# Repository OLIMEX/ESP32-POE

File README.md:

# ESP32-POE

ESP32-PoE is an IoT WIFI/BLE/Ethernet development board with Power-Over-Ethernet feature.

The Si3402-B chip is IEEE 802.3-compliant, including pre-standard (legacy) PoE support. 

Perfect solution for Internet-of-Things that can be expanded with sensors and actuators taking power from Ethernet cable.

Low-power design consuming less then 100uA in deep sleep mode!

Product page: https://www.olimex.com/Products/IoT/ESP32/ESP32-POE/open-source-hardware

## License
* Hardware is released under Apache 2.0 License
* Software is released under GPL3 License
* Documentation is released under CC BY-SA 3.0

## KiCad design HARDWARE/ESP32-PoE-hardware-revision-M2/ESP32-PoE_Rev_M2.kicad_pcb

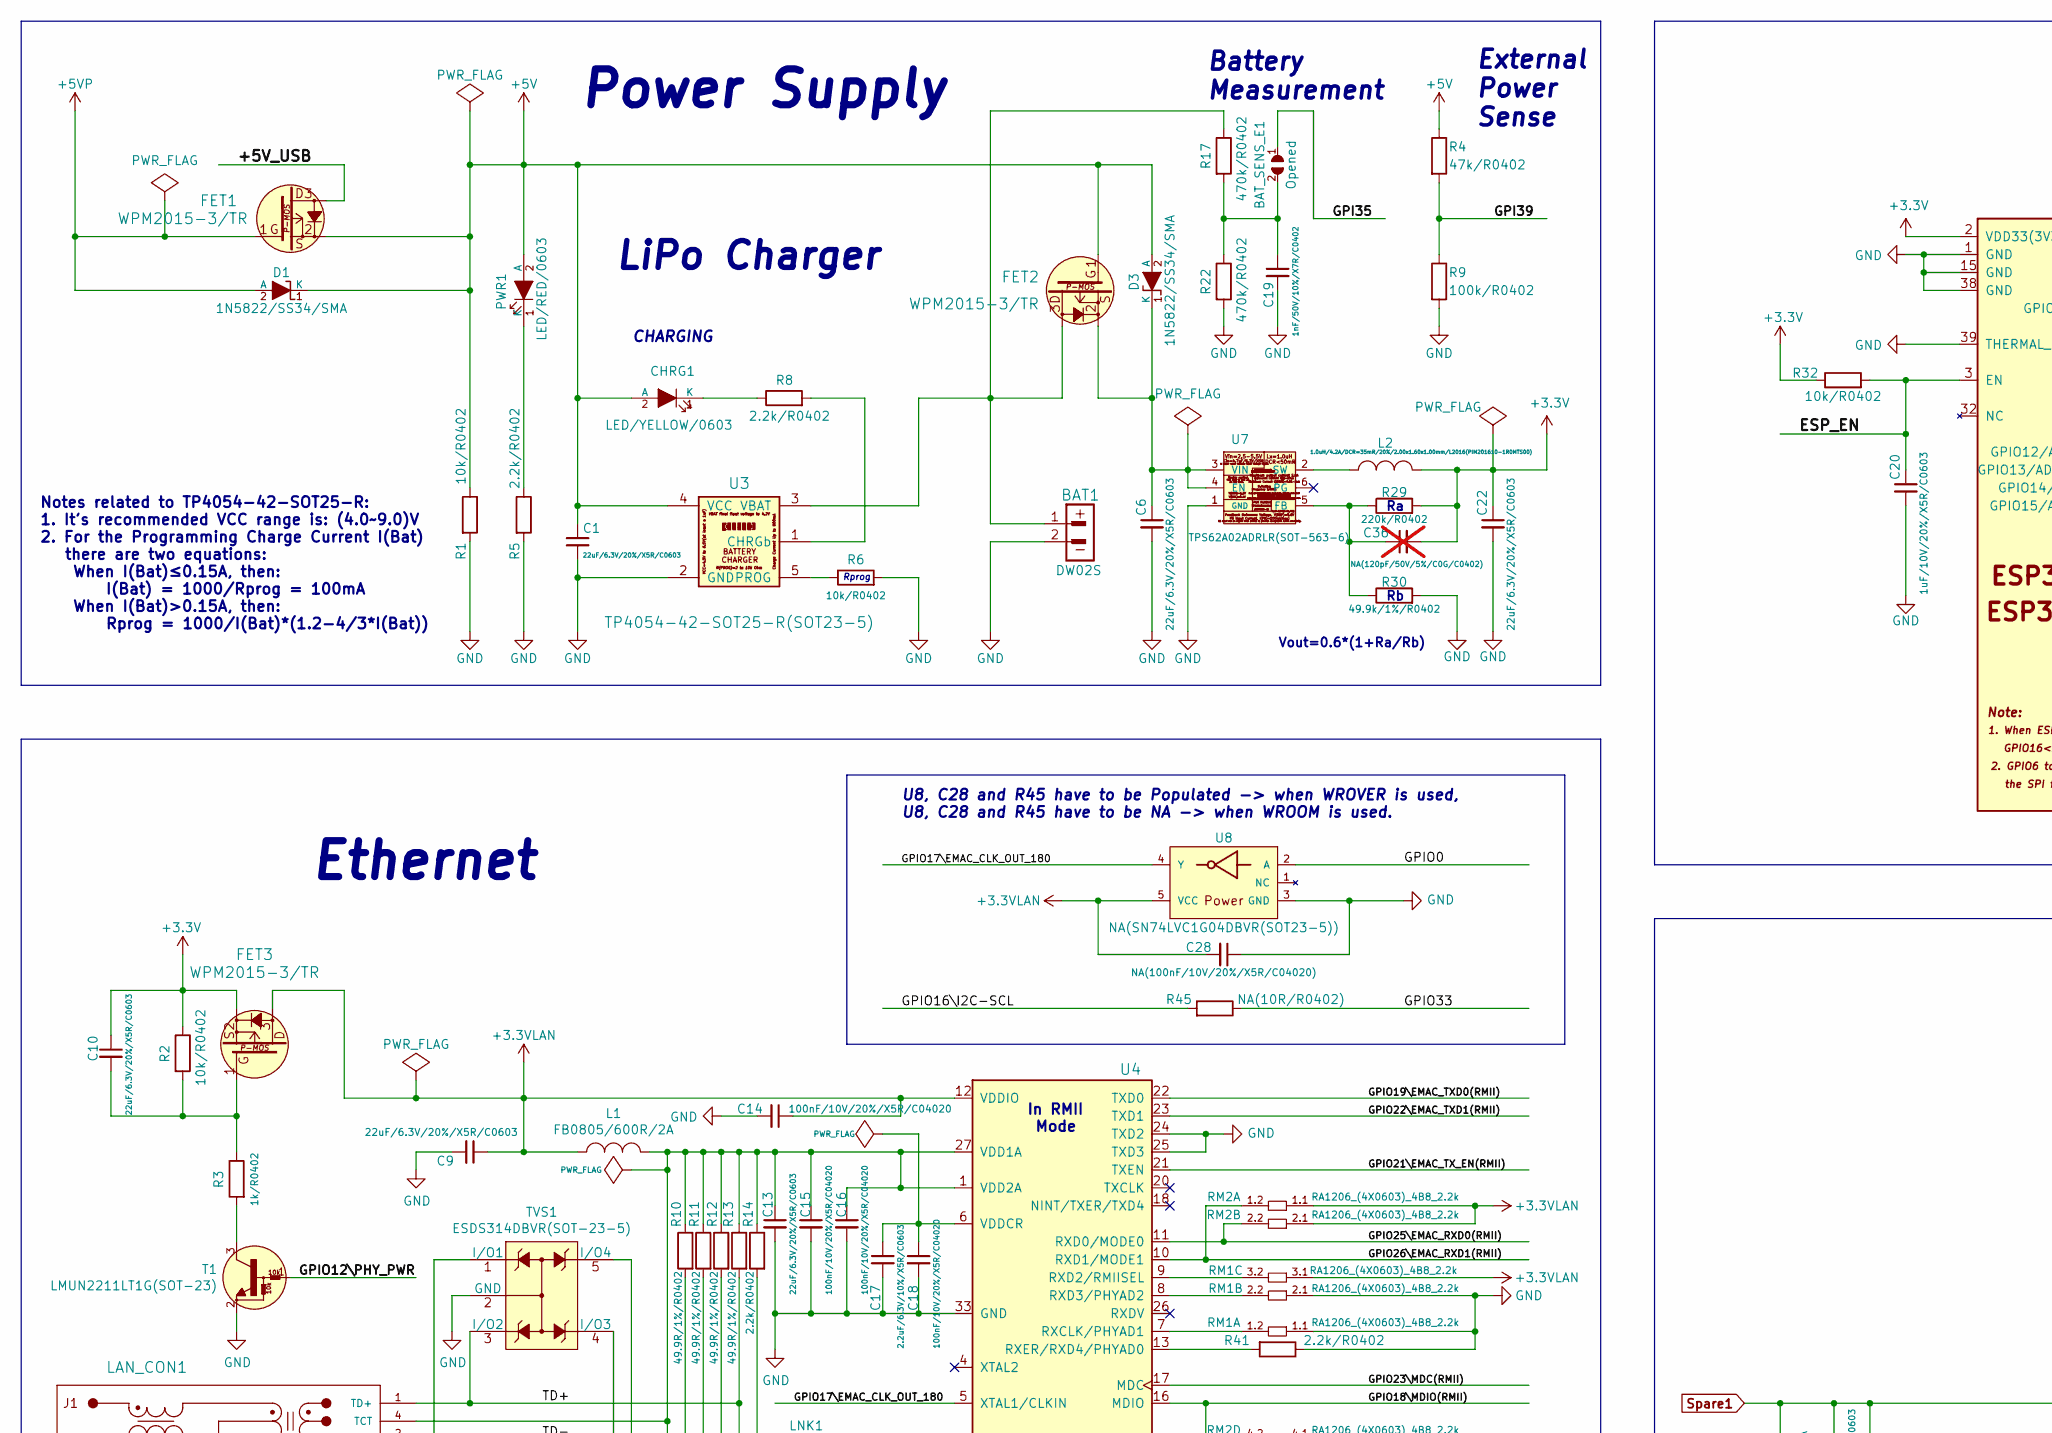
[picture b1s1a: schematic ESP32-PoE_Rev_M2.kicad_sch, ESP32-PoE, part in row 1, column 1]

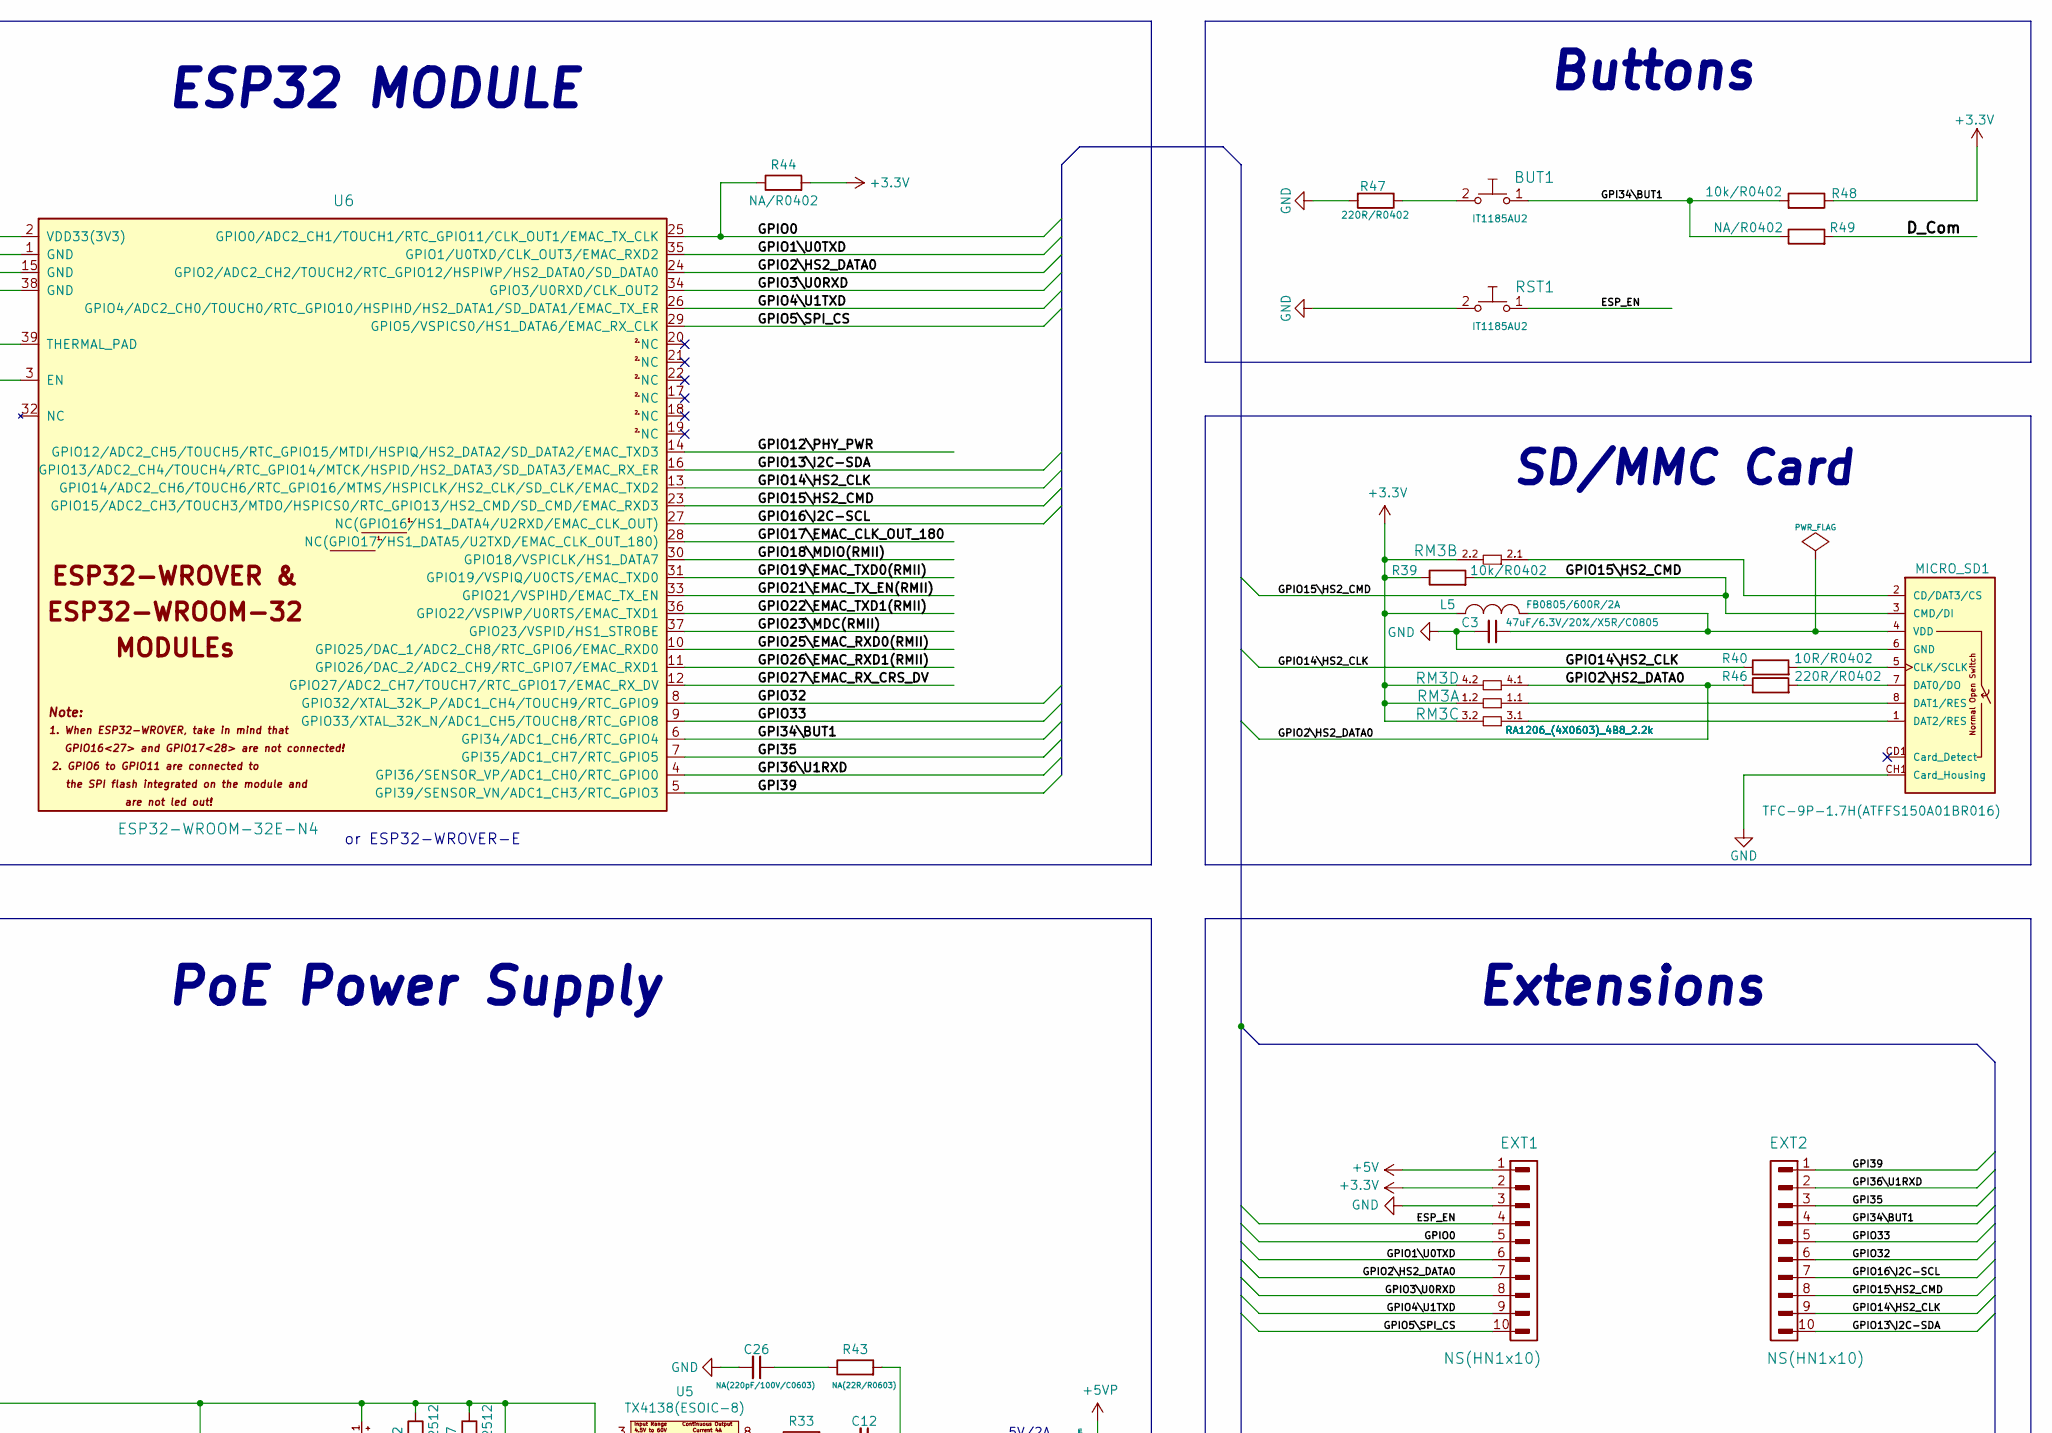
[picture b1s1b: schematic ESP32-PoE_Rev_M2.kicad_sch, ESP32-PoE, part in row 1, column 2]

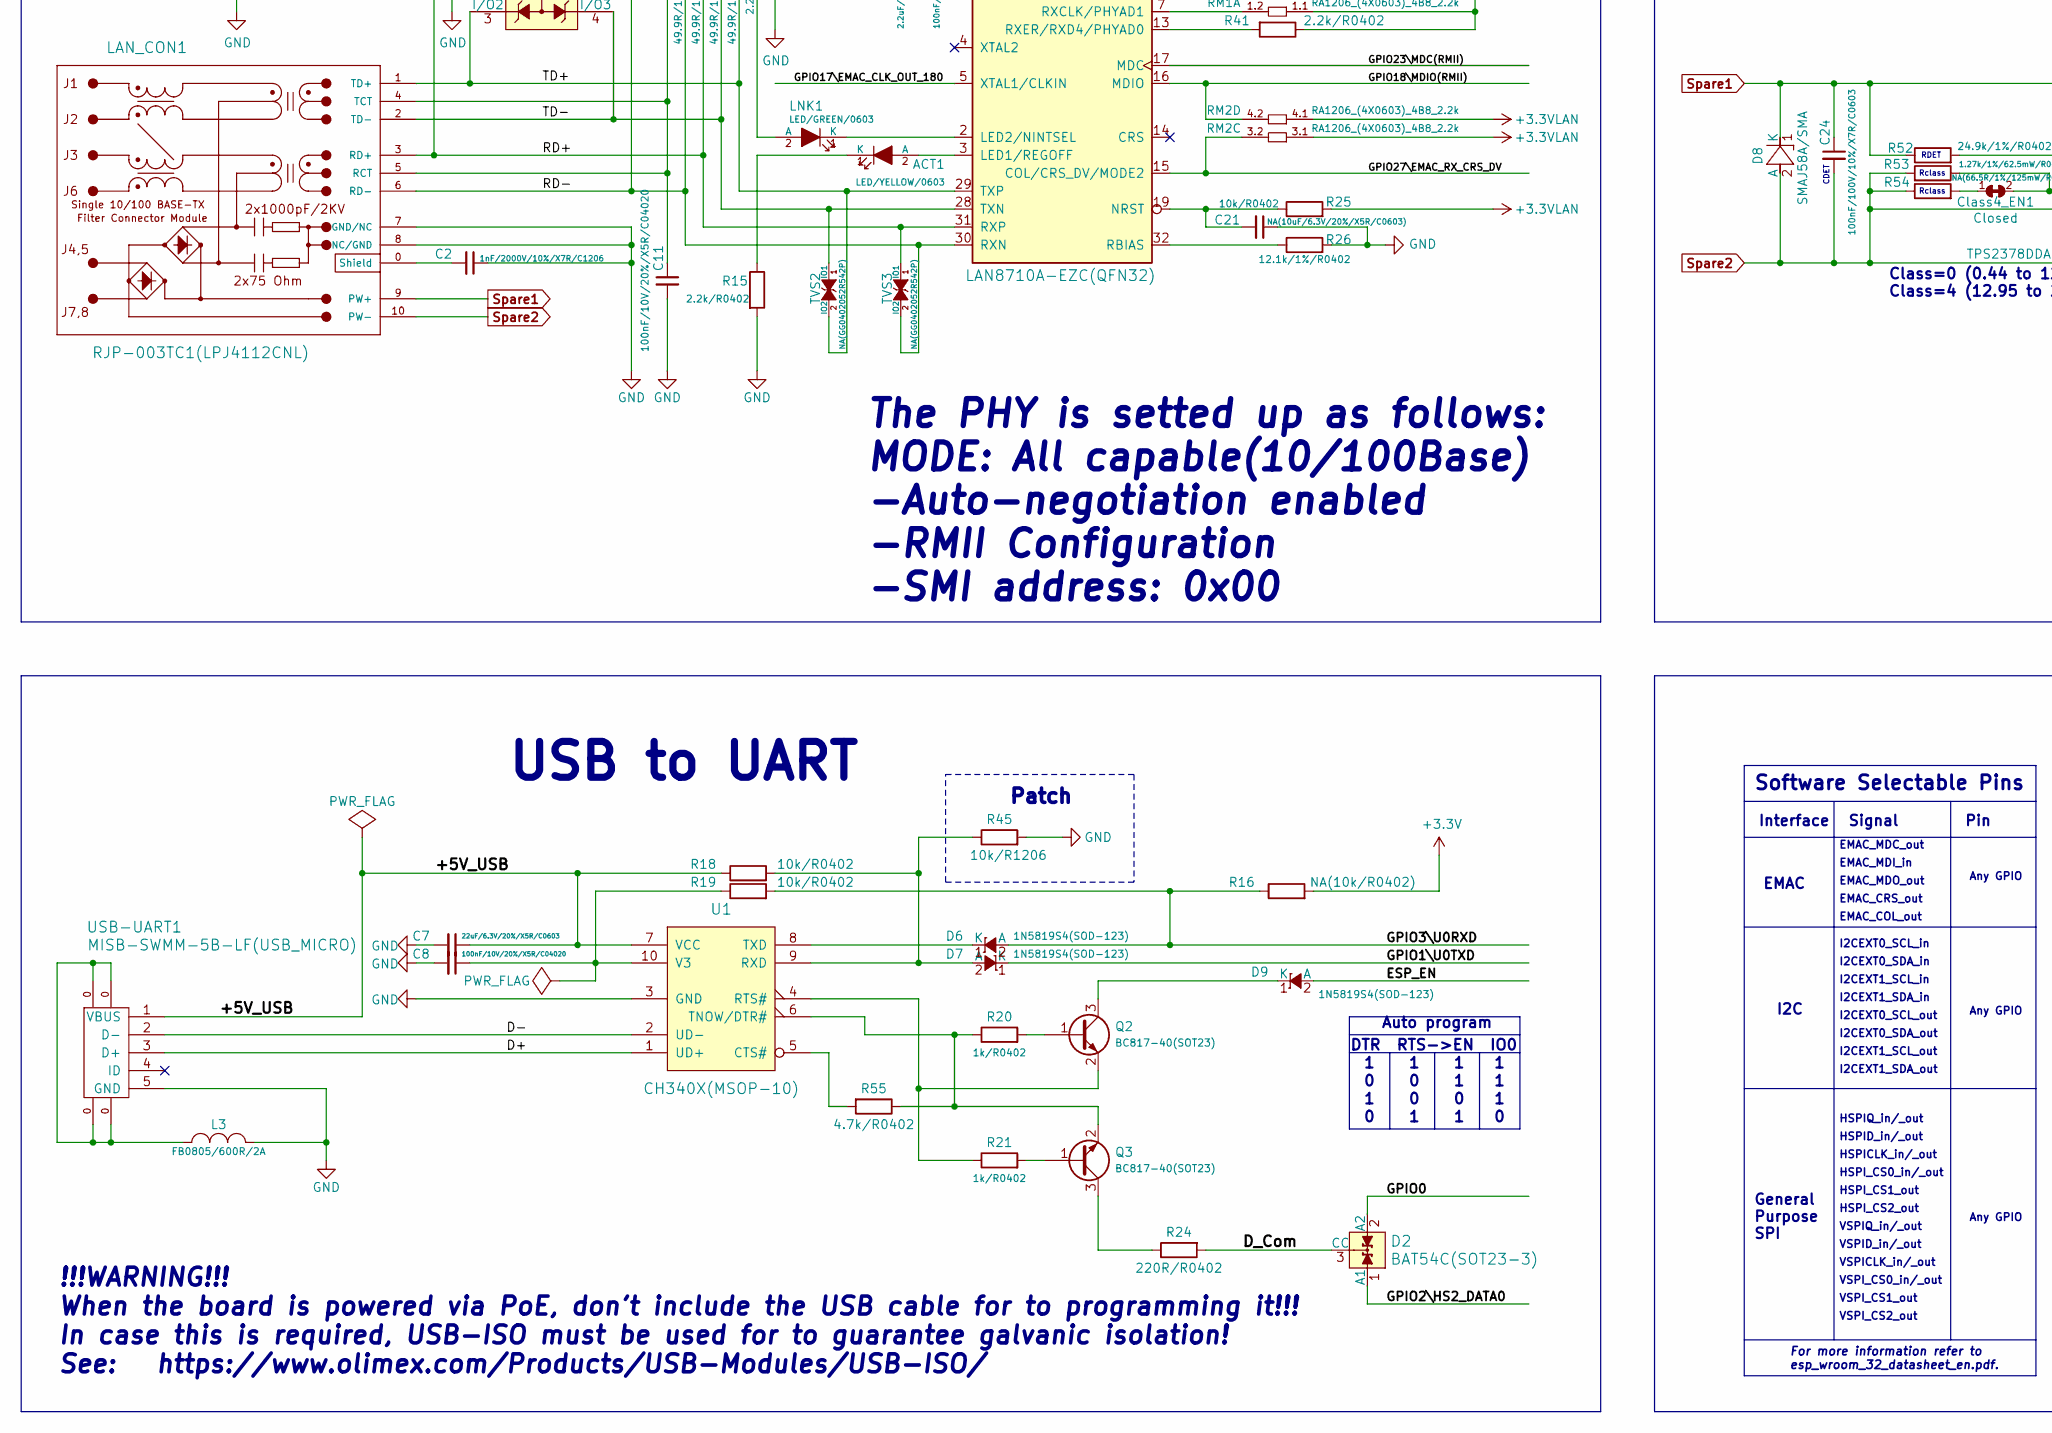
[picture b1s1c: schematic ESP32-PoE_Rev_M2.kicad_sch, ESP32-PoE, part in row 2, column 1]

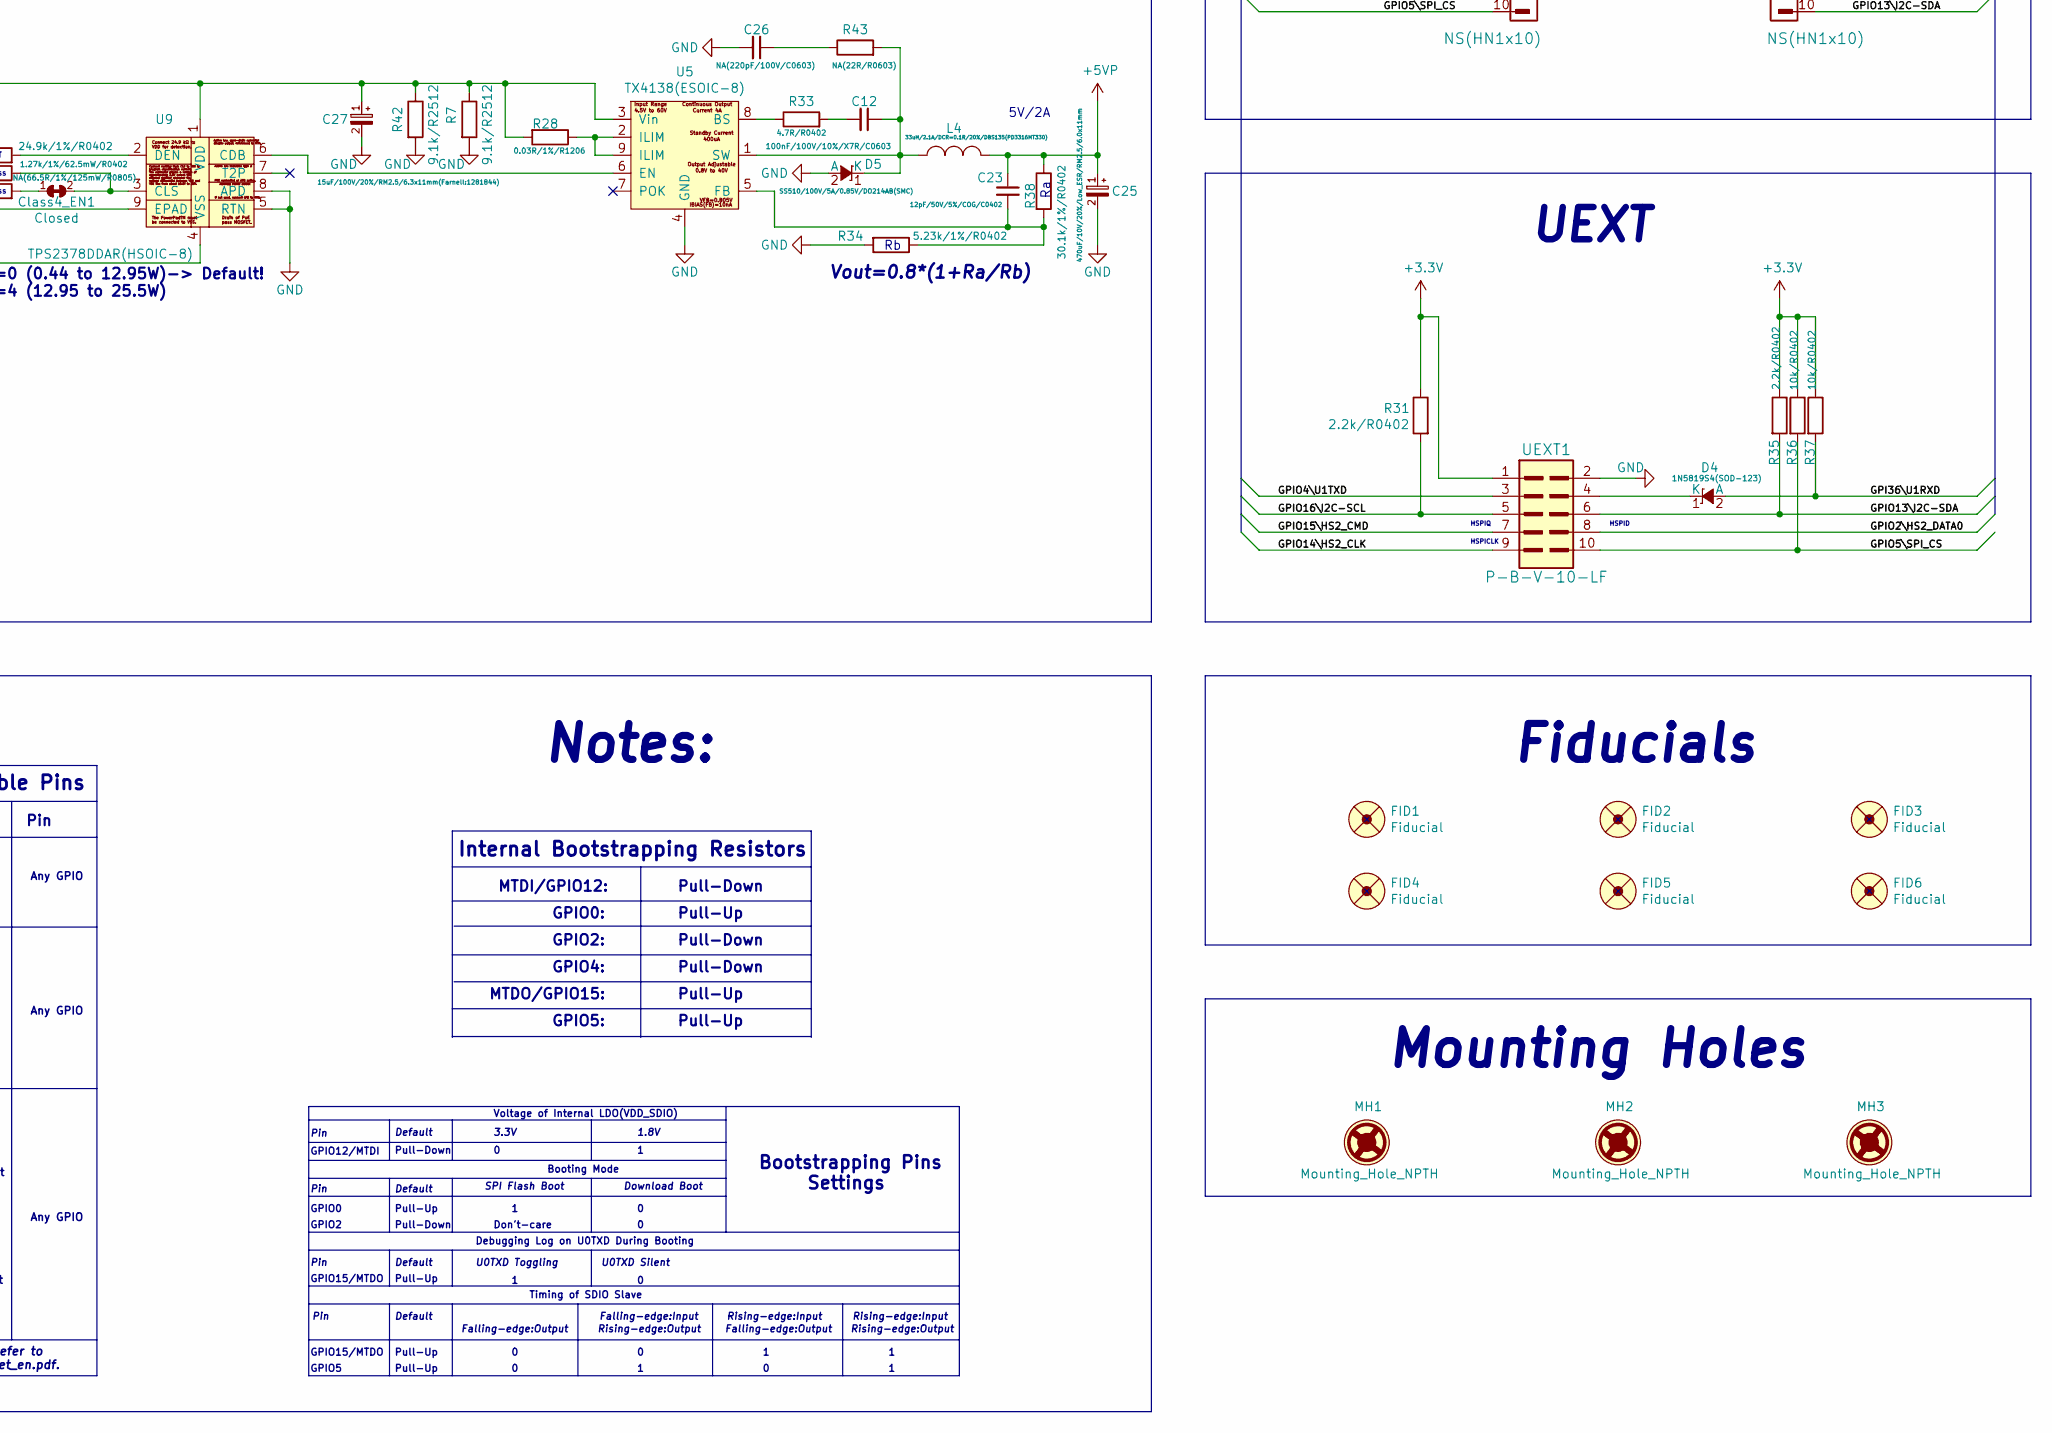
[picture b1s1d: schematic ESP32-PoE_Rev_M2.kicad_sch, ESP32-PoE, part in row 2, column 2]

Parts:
ACT1: LED/YELLOW/0603; LED_0603_KA
BAT1: DW02S; LIPO_BAT_VERTICAL_DW02S
BAT_SENS_E1: Opened; SJ_1_SMALLER
BUT1: IT1185AU2; IT1185AU2_V2
C1, C6, C7, C9, C10, C13, C22: 22uF/6.3V/20%/X5R/C0603; C_0603_5MIL_DWS
C2: 1nF/2000V/10%/X7R/C1206; C_1206_5MIL_DWS_ISO
C3: 47uF/6.3V/20%/X5R/C0805; C_0805_5MIL_DWS
C8, C11, C14, C15, C16, C18: 100nF/10V/20%/X5R/C04020; C_0402_5MIL_DWS
C12, C24: 100nF/100V/10%/X7R/C0603; C_0603_5MIL_DWS
C17: 2.2uF/6.3V/10%/X5R/C0603; C_0603_5MIL_DWS
C19: 1nF/50V/10%/X7R/C0402; C_0402_5MIL_DWS
C20: 1uF/10V/20%/X5R/C0603; C_0603_5MIL_DWS
C21: NA(10uF/6.3V/20%/X5R/C0603); C_0603_5MIL_DWS
C23: 12pF/50V/5%/COG/C0402; C_0402_5MIL_DWS
C25: 470uF/10V/20%/Low_ESR/RM2.5/6.0x11mm; CPOL-RM2.5mm_6.3x11mm_PTH
C26: NA(220pF/100V/C0603); C_0603_5MIL_DWS
C27: 15uF/100V/20%/RM2.5/6.3x11mm(Farnell:1281844); CPOL-RM2.5mm_6.3x11mm_PTH
C28: NA(100nF/10V/20%/X5R/C04020); C_0402_5MIL_DWS
C36: NA(120pF/50V/5%/C0G/C0402); C_0402_5MIL_DWS; not fitted
CHRG1: LED/YELLOW/0603; LED_0603_KA
Class4_EN1: Closed; SJ_Closed
D1, D3: 1N5822/SS34/SMA; SMA-KA
D2: BAT54C(SOT23-3); SOT23-3
D4, D6, D7, D9: 1N5819S4(SOD-123); SOD-123_1C-2A_KA
D5: SS510/100V/5A/0.85V/DO214AB(SMC); DO214AB(SMC)_1(K)-2(A)
D8: SMAJ58A/SMA; SMA-KA
EXT1, EXT2: NS(HN1x10); HN1x10
FET1, FET2, FET3: WPM2015-3/TR; SOT23
FID1, FID3, FID4, FID6: Fiducial; Fiducial1x3
FID2, FID5: Fiducial; Fiducial1x3_Paste
L1, L3, L5: FB0805/600R/2A; L_0805_5MIL_DWS
L2: 1.0uH/4.2A/DCR=35mR/20%/2.00x1.60x1.00mm/L2016(PI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; L_2016_MM
L4: 33uH/2.1A/DCR=0.1R/20%/DBS135(PD3316MT330); DBS135
LAN_CON1: RJP-003TC1(LPJ4112CNL)
LNK1: LED/GREEN/0603; LED_0603_KA
MH1, MH2, MH3: Mounting_Hole_NPTH; NPTH_2.2mm
MICRO_SD1: TFC-9P-1.7H(ATFFS150A01BR016); uSD(TFC-9P-1.xH(ATFFS150A01BR016))
PWR1: LED/RED/0603; LED_0603_KA
Q2, Q3: BC817-40(SOT23); SOT23
R1, R2, R6, R18, R19, R25, R32, R36, R37, R39, R48: 10k/R0402; R_0402_5MIL_DWS
R3, R20, R21: 1k/R0402; R_0402_5MIL_DWS
R4: 47k/R0402; R_0402_5MIL_DWS
R5, R8, R14, R15, R31, R35, R41: 2.2k/R0402; R_0402_5MIL_DWS
R7, R42: 9.1k/R2512; R_2512_MM_DWS
R9: 100k/R0402; R_0402_5MIL_DWS
R10, R11, R12, R13: 49.9R/1%/R0402; R_0402_5MIL_DWS
R16: NA(10k/R0402); R_0402_5MIL_DWS
R17, R22: 470k/R0402; R_0402_5MIL_DWS
R24, R46, R47: 220R/R0402; R_0402_5MIL_DWS
R26: 12.1k/1%/R0402; R_0402_5MIL_DWS
R28: 0.03R/1%/R1206; R_1206_5MIL_DWS
R29: 220k/R0402; R_0402_5MIL_DWS
R30: 49.9k/1%/R0402; R_0402_5MIL_DWS
R33: 4.7R/R0402; R_0402_5MIL_DWS
R34: 5.23k/1%/R0402; R_0402_5MIL_DWS
R38: 30.1k/1%/R0402; R_0402_5MIL_DWS
R40: 10R/R0402; R_0402_5MIL_DWS
R43: NA(22R/R0603); R_0603_5MIL_DWS
R44, R49: NA/R0402; R_0402_5MIL_DWS
R45: NA(10R/R0402); R_0402_5MIL_DWS
R52: 24.9k/1%/R0402; R_0402_5MIL_DWS
R53: 1.27k/1%/62.5mW/R0402; R_0402_5MIL_DWS
R54: NA(66.5R/1%/125mW/R0805); R_0805_5MIL_DWS
R55: 4.7k/R0402; R_0402_5MIL_DWS
RM1, RM2, RM3: RA1206_(4X0603)_4B8_2.2k; R_MATRIX_4
RST1: IT1185AU2; IT1185AU2_V2
T1: LMUN2211LT1G(SOT-23); SOT23
TVS1: ESDS314DBVR(SOT-23-5); SOT-23-5
TVS2, TVS3: NA(GG0402052R542P); D_0402_5MIL_DWS
U1: CH340X(MSOP-10); MSOP-10_Pitch-0.5mm_3.00x3.00x1.00mm
U3: TP4054-42-SOT25-R(SOT23-5); SOT-23-5
U4: LAN8710A-EZC(QFN32); QFN32_EP(33)_5.00x5.00x0.90mm_Pitch_0.50mm
U5: TX4138(ESOIC-8); ESOIC-8
U6: ESP32-WROOM-32E-N4; ESP32-WROVER_MODULE
U7: TPS62A02ADRLR(SOT-563-6); SOT-563-6
U8: NA(SN74LVC1G04DBVR(SOT23-5)); SOT-23-5
U9: TPS2378DDAR(HSOIC-8); ESOIC-8
UEXT1: P-B-V-10-LF; GBH-254-SMT-10
USB-UART1: MISB-SWMM-5B-LF(USB_MICRO); USB-MICRO_MISB-SWMM-5B_LF

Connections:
+3.3V: C10.1, C22.1, EXT1.2, FET3.2, L2.2, L5.1, R2.1, R16.2, R29.2, R31.1, R32.1, R35.1, R36.1, R37.1, R39.1, R44.2, R48.1, RM3.1.2, RM3.2.2, RM3.3.2, RM3.4.2, U6.2 (VDD33(3V3)), UEXT1.1; also elsewhere on the board
+3.3VLAN: C9.1, C14.1, C28.2, FET3.3, L1.1, R25.2, RM1.3.1, RM2.1.1, RM2.2.1, RM2.3.1, RM2.4.1, U4.12 (VDDIO), U8.5 (VCC)
+5V: C1.1, CHRG1.2 (A), D1.1 (K), D3.2 (A), EXT1.1, FET1.2, FET2.1, PWR1.2 (A), R1.1, R4.1, U3.4 (VCC)
+5VP: C23.1, C25.1 (+), D1.2 (A), FET1.1, L4.2, R38.1
/+5V_USB: C7.1, FET1.3, R18.1, U1.7 (VCC), USB-UART1.1 (VBUS)
/D+: U1.1 (UD+), USB-UART1.3 (D+)
/D-: U1.2 (UD-), USB-UART1.2 (D-)
/D_Com: D2.3 (CC), R24.2, R49.2
/ESP_EN: C20.1, D9.2 (A), EXT1.4, R32.2, RST1.1, U6.3 (EN)
/GPI34\BUT1: BUT1.1, EXT2.4, R48.2, R49.1, U6.6 (GPI34/ADC1_CH6/RTC_GPIO4)
/GPI35: BAT_SENS_E1.1, EXT2.3, U6.7 (GPI35/ADC1_CH7/RTC_GPIO5)
/GPI36\U1RXD: D4.2 (A), EXT2.2, R37.2, U6.4 (GPI36/SENSOR_VP/ADC1_CH0/RTC_GPIO0)
/GPI39: EXT2.1, R4.2, R9.1, U6.5 (GPI39/SENSOR_VN/ADC1_CH3/RTC_GPIO3)
/GPIO0: D2.2 (A2), EXT1.5, R44.1, U6.25 (GPIO0/ADC2_CH1/TOUCH1/RTC_GPIO11/CLK_OU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), U8.2 (A)
/GPIO1\U0TXD: D7.1 (K), EXT1.6, U6.35 (GPIO1/U0TXD/CLK_OUT3/EMAC_RXD2)
/GPIO2\HS2_DATA0: D2.1 (A1), EXT1.7, R46.1, RM3.4.1, U6.24 (GPIO2/ADC2_CH2/TOUCH2/RTC_GPIO12/HSPIWP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), UEXT1.8
/GPIO3\U0RXD: D6.2 (A), EXT1.8, R16.1, R19.2, U6.34 (GPIO3/U0RXD/CLK_OUT2)
/GPIO4\U1TXD: EXT1.9, U6.26 (GPIO4/ADC2_CH0/TOUCH0/RTC_GPIO10/HSPIHD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), UEXT1.3
/GPIO5\SPI_CS: EXT1.10, R36.2, U6.29 (GPIO5/VSPICS0/HS1_DATA6/EMAC_RX_CLK), UEXT1.10
/GPIO12\PHY_PWR: T1.1 (B), U6.14 (GPIO12/ADC2_CH5/TOUCH5/RTC_GPIO15/MTDI/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)
/GPIO13\I2C-SDA: EXT2.10, R35.2, U6.16 (GPIO13/ADC2_CH4/TOUCH4/RTC_GPIO14/MTCK/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), UEXT1.6
/GPIO14\HS2_CLK: EXT2.9, R40.1, U6.13 (GPIO14/ADC2_CH6/TOUCH6/RTC_GPIO16/MTMS/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), UEXT1.9
/GPIO15\HS2_CMD: EXT2.8, MICRO_SD1.3 (CMD/DI), R39.2, U6.23 (GPIO15/ADC2_CH3/TOUCH3/MTDO/HSPICS0/RTC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), UEXT1.7
/GPIO17\EMAC_CLK_OUT_180: U4.5 (XTAL1/CLKIN), U6.28 (NC(GPIO17/HS1_DATA5/U2TXD/EMAC_CLK_OUT_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), U8.4 (Y)
/GPIO18\MDIO(RMII): RM2.4.2, U4.16 (MDIO), U6.30 (GPIO18/VSPICLK/HS1_DATA7)
/GPIO19\EMAC_TXD0(RMII): U4.22 (TXD0), U6.31 (GPIO19/VSPIQ/U0CTS/EMAC_TXD0)
/GPIO21\EMAC_TX_EN(RMII): U4.21 (TXEN), U6.33 (GPIO21/VSPIHD/EMAC_TX_EN)
/GPIO22\EMAC_TXD1(RMII): U4.23 (TXD1), U6.36 (GPIO22/VSPIWP/U0RTS/EMAC_TXD1)
/GPIO23\MDC(RMII): U4.17 (MDC), U6.37 (GPIO23/VSPID/HS1_STROBE)
/GPIO25\EMAC_RXD0(RMII): RM2.2.2, U4.11 (RXD0/MODE0), U6.10 (GPIO25/DAC_1/ADC2_CH8/RTC_GPIO6/EMAC_RX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)
/GPIO26\EMAC_RXD1(RMII): RM2.1.2, U4.10 (RXD1/MODE1), U6.11 (GPIO26/DAC_2/ADC2_CH9/RTC_GPIO7/EMAC_RX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)
/GPIO27\EMAC_RX_CRS_DV: RM2.3.2, U4.15 (COL/CRS_DV/MODE2), U6.12 (GPIO27/ADC2_CH7/TOUCH7/RTC_GPIO17/EMAC_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)
/GPIO32: EXT2.6, U6.8 (GPIO32/XTAL_32K_P/ADC1_CH4/TOUCH9/RTC_G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)
/RD+: LAN_CON1.3 (RD+), R11.2, TVS1.1 (I/O1), TVS3.1 (IO1), U4.31 (RXP)
/RD-: LAN_CON1.6 (RD-), R10.2, TVS1.5 (I/O4), TVS3.2 (IO2), U4.30 (RXN)
/TD+: LAN_CON1.1 (TD+), R13.2, TVS1.3 (I/O2), TVS2.2 (IO2), U4.29 (TXP)
/TD-: LAN_CON1.2 (TD-), R12.2, TVS1.4 (I/O3), TVS2.1 (IO1), U4.28 (TXN)
unnamed: ACT1.2 (A), U4.3 (LED1/REGOFF)
unnamed: ACT1.1 (K), R15.1
unnamed: BAT_SENS_E1.2, C19.1, R17.2, R22.1
unnamed: BUT1.2, R47.1
unnamed: C10.2, FET3.1, R2.2, R3.1
unnamed: C12.2, R33.2
unnamed: C26.1, R43.1
unnamed: CHRG1.1 (K), R8.1
unnamed: Class4_EN1.1, R54.2
unnamed: C6.1, D3.1 (K), FET2.2, U7.3 (VIN), U7.4 (EN)
unnamed: D4.1 (K), UEXT1.4
unnamed: C12.1, D5.1 (K), L4.1, R43.2, U5.1 (SW)
unnamed: D6.1 (K), U1.8 (TXD)
unnamed: D9.1 (K), Q2.3 (C)
unnamed: L3.1, USB-UART1.0
unnamed: C11.1, C13.1, C15.1, C16.1, L1.2, LAN_CON1.4 (TCT), LAN_CON1.5 (RCT), R10.1, R11.1, R12.1, R13.1, R14.1, U4.1 (VDD2A), U4.27 (VDD1A)
unnamed: C2.2, LAN_CON1.0 (Shield)
unnamed: LNK1.2 (A), R14.2
unnamed: LNK1.1 (K), U4.2 (LED2/NINTSEL)
unnamed: MICRO_SD1.2 (CD/DAT3/CS), RM3.2.1
unnamed: MICRO_SD1.5 (CLK/SCLK), R40.2
unnamed: MICRO_SD1.7 (DAT0/DO), R46.2
unnamed: MICRO_SD1.8 (DAT1/RES), RM3.1.1
unnamed: MICRO_SD1.1 (DAT2/RES), RM3.3.1
unnamed: C3.1, L5.2, MICRO_SD1.4 (VDD)
unnamed: PWR1.1 (K), R5.1
unnamed: Q2.1 (B), R20.2
unnamed: Q2.2 (E), R21.1, U1.4 (RTS#)
unnamed: Q3.1 (B), R21.2
unnamed: Q3.3 (C), R24.1
unnamed: Q3.2 (E), R20.1, R55.1, U1.6 (TNOW/DTR#)
unnamed: R28.1, U5.2 (ILIM), U5.9 (ILIM)
unnamed: R3.2, T1.3 (C)
unnamed: R55.2, U1.5 (CTS#)
unnamed: C8.1, R19.1, U1.10 (V3)
unnamed: R8.2, U3.1 (CHRGb)
unnamed: R6.1, U3.5 (PROG)
unnamed: BAT1.1, FET2.3, R17.1, U3.3 (VBAT)
unnamed: C21.2, R25.1, U4.19 (NRST)
unnamed: R26.1, U4.32 (RBIAS)
unnamed: RM1.1.2, U4.7 (RXCLK/PHYAD1)
unnamed: RM1.3.2, U4.9 (RXD2/RMIISEL)
unnamed: RM1.2.2, U4.8 (RXD3/PHYAD2)
unnamed: R41.2, U4.13 (RXER/RXD4/PHYAD0)
unnamed: C17.1, C18.1, U4.6 (VDDCR)
unnamed: R33.1, U5.8 (BS)
unnamed: U5.6 (EN), U9.6 (CDB)
unnamed: C23.2, R34.1, R38.2, U5.5 (FB)
unnamed 85: R29.1, R30.1, U7.5 (FB); also elsewhere on the board
unnamed: L2.1, U7.2 (SW)
unnamed: Class4_EN1.2, R53.1, U9.3 (CLS)
unnamed: R52.2, U9.2 (DEN)
Spare1: C24.1, C27.1 (+), D8.1 (K), LAN_CON1.9 (PW+), R7.1, R28.2, R42.1, R52.1, U5.3 (Vin), U9.1 (VDD)
Spare2: C24.2, D8.2 (A), LAN_CON1.10 (PW-), R53.2, R54.1, U9.4 (VSS), U9.9 (EPAD)

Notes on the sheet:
Pull-Up
Pull-Down
GPIO2:
Rising-edge:Output
HSPID
Pin
MTDO/GPIO15:
HSPI_CS1_out
Don't-care
Rprog
HSPICLK
PoE Power Supply
EMAC_COL_out
Fiducials
GPIO15/MTDO
I2CEXT0_SCL_in
I2C
I2CEXT1_SCL_in
DTR RTS->EN IO0
Software Selectable Pins
CHARGING
Rising-edge:Input
The PHY is setted up as follows: MODE: All capable(10/100Base) -Auto-negotiation enabled -RMII Configuration -SMI address: 0x00
LiPo Charger
EMAC
GPIO5
Signal
Timing of SDIO Slave
Internal Bootstrapping Resistors
Buttons
Notes:
GPIO0
I2CEXT1_SDA_in
VSPI_CS0_in/_out
Vout=0.6*(1+Ra/Rb)
RDET
MTDI/GPIO12:
Default
HSPID_in/_out
VSPI_CS2_out

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
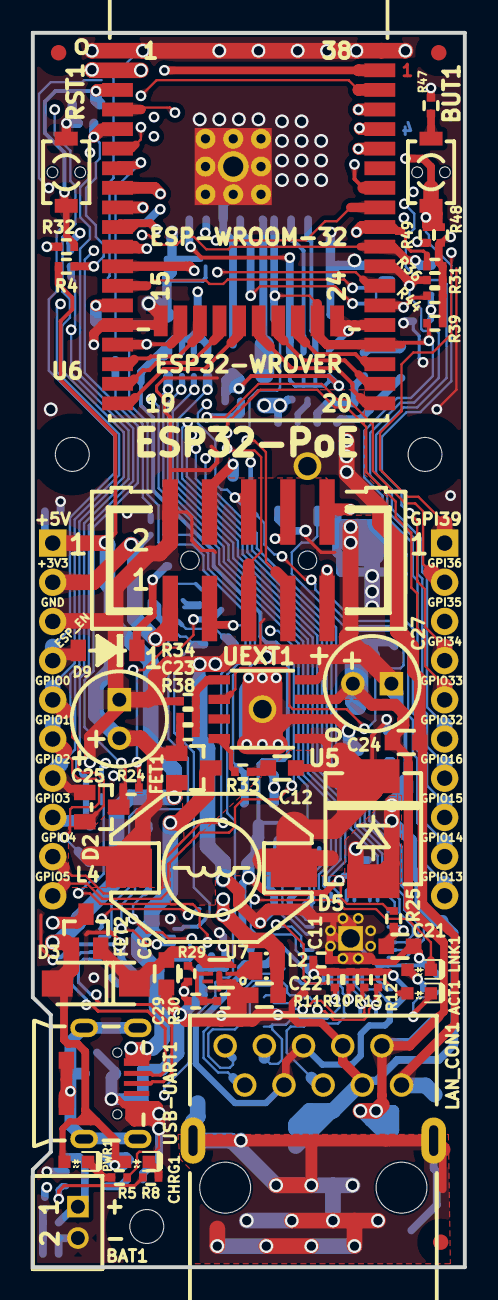
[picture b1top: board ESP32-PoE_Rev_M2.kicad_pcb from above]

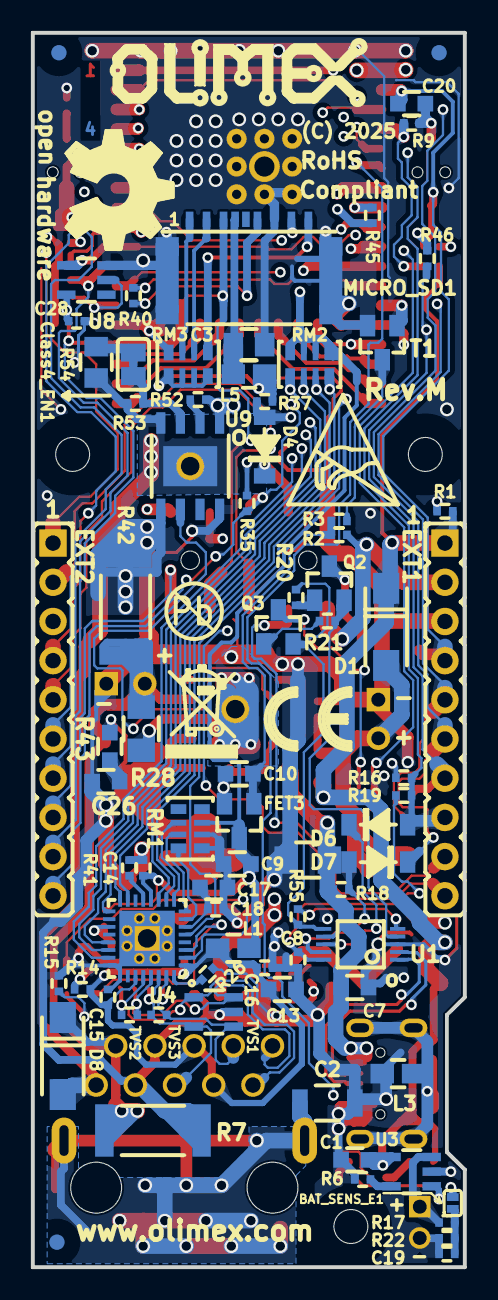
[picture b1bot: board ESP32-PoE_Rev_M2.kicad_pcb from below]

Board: 4 copper layers, 28.0 x 80.0 mm, 143 parts (84 on the bottom side), 95 nets.

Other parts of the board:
C29: NA(120pF/50V/5%/C0G/C0402); C_0402_5MIL_DWS
CE: CE_Sign
Logo_OSHW: LOGO_OPENHARDWARE_8x8
Logo_Olimex: OLIMEX_LOGO_TB
R23: 10k/R1206; R_1206_5MIL_DWS
Sign_Antistatic: Val**; LOGO_ANTISTATIC_1
Sign_PB-Free: LOGO_PBFREE
Sign_RecycleBin: LOGO_RECYCLEBIN_1

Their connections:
+3.3V: C29.2; also elsewhere on the board
unnamed 85: C29.1; also elsewhere on the board

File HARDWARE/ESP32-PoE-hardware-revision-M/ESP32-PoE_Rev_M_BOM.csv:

"Id";"Designator";"Footprint";"Quantity";"Designation";"Supplier and ref";
1;"FID3,FID1,FID6,FID4";"Fiducial1x3";4;"Fiducial";;;
2;"UEXT1";"GBH-254-SMT-10";1;"P-B-V-10-LF";;;
3;"D2";"SOT23-3";1;"BAT54C(SOT23-3)";;;
4;"FET2,FET1,FET3";"SOT23";3;"WPM2015-3/TR";;;
5;"R48,R39,R32,R25,R36,R1,R6,R18,R19,R2,R37";"R_0402_5MIL_DWS";11;"10k/R0402";;;
6;"R47,R24,R46";"R_0402_5MIL_DWS";3;"220R/R0402";;;
7;"R31,R8,R5,R14,R35,R15,R41";"R_0402_5MIL_DWS";7;"2.2k/R0402";;;
8;"R4";"R_0402_5MIL_DWS";1;"47k/R0402";;;
9;"CHRG1,ACT1";"LED_0603_KA";2;"LED/YELLOW/0603";;;
10;"R13,R10,R12,R11";"R_0402_5MIL_DWS";4;"49.9R/1%/R0402";;;
11;"R44,R49";"R_0402_5MIL_DWS";2;"NA/R0402";;;
12;"LAN_CON1";"RJP-003TC1(LPJ4112CNL)";1;"RJP-003TC1(LPJ4112CNL)";;;
13;"C21";"C_0603_5MIL_DWS";1;"NA(10uF/6.3V/20%/X5R/C0603)";;;
14;"C22,C6,C9,C1,C7,C10,C13";"C_0603_5MIL_DWS";7;"22uF/6.3V/20%/X5R/C0603";;;
15;"R33";"R_0402_5MIL_DWS";1;"4.7R/R0402";;;
16;"D9,D4,D6,D7";"SOD-123_1C-2A_KA";4;"1N5819S4(SOD-123)";;;
17;"C12,C24";"C_0603_5MIL_DWS";2;"100nF/100V/10%/X7R/C0603";;;
18;"RST1,BUT1";"IT1185AU2_V2";2;"IT1185AU2";;;
19;"C23";"C_0402_5MIL_DWS";1;"12pF/50V/5%/COG/C0402";;;
20;"R34";"R_0402_5MIL_DWS";1;"5.23k/1%/R0402";;;
21;"R38";"R_0402_5MIL_DWS";1;"30.1k/1%/R0402";;;
22;"L2";"L_2016_MM";1;"1.0uH/4.2A/DCR=35mR/20%/2.00x1.60x1.00mm/L2016(PIM201610-1R0MTS00)";;;
23;"FID2,FID5";"Fiducial1x3_Paste";2;"Fiducial";;;
24;"C27";"CPOL-RM2.5mm_6.3x11mm_PTH";1;"15uF/100V/20%/RM2.5/6.3x11mm(Farnell:1281844)";;;
25;"D5";"DO214AB(SMC)_1(K)-2(A)";1;"SS510/100V/5A/0.85V/DO214AB(SMC)";;;
26;"C25";"CPOL-RM2.5mm_6.3x11mm_PTH";1;"470uF/10V/20%/Low_ESR/RM2.5/6.0x11mm";;;
27;"L4";"DBS135";1;"33uH/2.1A/DCR=0.1R/20%/DBS135(PD3316MT330)";;;
28;"R29";"R_0402_5MIL_DWS";1;"220k/R0402";;;
29;"R30";"R_0402_5MIL_DWS";1;"49.9k/1%/R0402";;;
30;"D3,D1";"SMA-KA";2;"1N5822/SS34/SMA";;;
31;"USB-UART1";"USB-MICRO_MISB-SWMM-5B_LF";1;"MISB-SWMM-5B-LF(USB_MICRO)";;;
32;"U7";"SOT-563-6";1;"TPS62A02ADRLR(SOT-563-6)";;;
33;"C11,C15,C16,C18,C8,C14,C28";"C_0402_5MIL_DWS";7;"100nF/16V/10%/X7R/C0402";;;
34;"LNK1";"LED_0603_KA";1;"LED/GREEN/0603";;;
35;"U5";"ESOIC-8";1;"TX4138(ESOIC-8)";;;
36;"U6";"ESP32-WROVER_MODULE";1;"ESP32-WROVER-E";;;
37;"MH1,MH2,MH3";"NPTH_2.2mm";3;"Mounting_Hole_NPTH";;;
38;"BAT1";"LIPO_BAT_VERTICAL_DW02S";1;"DW02S";;;
39;"PWR1";"LED_0603_KA";1;"LED/RED/0603";;;
40;"C29";"C_0402_5MIL_DWS";1;"NA(120pF/50V/5%/C0G/C0402)";;;
41;"EXT2,EXT1";"HN1x10";2;"NS(HN1x10)";;;
42;"RM1,RM2,RM3";"R_MATRIX_4";3;"RA1206_(4X0603)_4B8_2.2k";;;
43;"MICRO_SD1";"uSD(TFC-9P-1.xH(ATFFS150A01BR016))";1;"TFC-9P-1.7H(ATFFS150A01BR016)";;;
44;"R40,R45";"R_0402_5MIL_DWS";2;"10R/R0402";;;
45;"C3";"C_0805_5MIL_DWS";1;"47uF/6.3V/20%/X5R/C0805";;;
46;"C17";"C_0603_5MIL_DWS";1;"2.2uF/6.3V/10%/X5R/C0603";;;
47;"L1,L3,L5";"L_0805_5MIL_DWS";3;"FB0805/600R/2A";;;
48;"R22,R17";"R_0402_5MIL_DWS";2;"470k/R0402";;;
49;"C19";"C_0402_5MIL_DWS";1;"1nF/50V/10%/X7R/C0402";;;
50;"BAT_SENS_E1";"SJ_1_SMALLER";1;"Opened";;;
51;"Sign_Antistatic";"LOGO_ANTISTATIC_1";1;"Val**";;;
52;"Sign_RecycleBin";"LOGO_RECYCLEBIN_1";1;"";;;
53;"Sign_PB-Free";"LOGO_PBFREE";1;"";;;
54;"Logo_OSHW";"LOGO_OPENHARDWARE_8x8";1;"";;;
55;"C2";"C_1206_5MIL_DWS_ISO";1;"1nF/2000V/10%/X7R/C1206";;;
56;"D8";"SMA-KA";1;"SMAJ58A/SMA";;;
57;"Q2,Q3";"SOT23";2;"BC817-40(SOT23)";;;
58;"R21,R20,R3";"R_0402_5MIL_DWS";3;"1k/R0402";;;
59;"R16";"R_0402_5MIL_DWS";1;"NA(10k/R0402)";;;
60;"Logo_Olimex";"OLIMEX_LOGO_TB";1;"";;;
61;"TVS2,TVS3";"D_0402_5MIL_DWS";2;"NA(GG0402052R542P)";;;
62;"TVS1";"SOT-23-5";1;"ESDS314DBVR(SOT-23-5)";;;
63;"U4";"QFN32_EP(33)_5.00x5.00x0.90mm_Pitch_0.50mm";1;"LAN8710A-EZC(QFN32)";;;
64;"R26";"R_0402_5MIL_DWS";1;"12.1k/1%/R0402";;;
65;"R28";"R_1206_5MIL_DWS";1;"0.03R/1%/R1206";;;
66;"R9";"R_0402_5MIL_DWS";1;"100k/R0402";;;
67;"CE";"CE_Sign";1;"CE_Sign";;;
68;"R42,R7";"R_2512_MM_DWS";2;"9.1k/R2512";;;
69;"C26";"C_0603_5MIL_DWS";1;"NA(220pF/100V/C0603)";;;
70;"R43";"R_0603_5MIL_DWS";1;"NA(22R/R0603)";;;
71;"U8";"SOT-23-5";1;"SN74LVC1G04DBVR(SOT23-5)";;;
72;"U3";"SOT-23-5";1;"TP4054-42-SOT25-R(SOT23-5)";;;
73;"T1";"SOT23";1;"LMUN2211LT1G(SOT-23)";;;
74;"C20";"C_0603_5MIL_DWS";1;"1uF/10V/20%/X5R/C0603";;;
75;"R52";"R_0402_5MIL_DWS";1;"24.9k/1%/R0402";;;
76;"R54";"R_0805_5MIL_DWS";1;"66.5R/1%/125mW/R0805";;;
77;"U1";"MSOP-10_Pitch-0.5mm_3.00x3.00x1.00mm";1;"CH340X(MSOP-10)";;;
78;"R55";"R_0402_5MIL_DWS";1;"4.7k/R0402";;;
79;"Class4_EN1";"SJ_Closed";1;"Closed";;;
80;"R53";"R_0402_5MIL_DWS";1;"1.27k/1%/62.5mW/R0402";;;
81;"U9";"ESOIC-8";1;"TPS2378DDAR(HSOIC-8)";;;

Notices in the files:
HARDWARE/ESP32-PoE-hardware-revision-E/BackupFiles/ESP32-PoE_Rev_E.kicad_pcb:
(C) 2020
